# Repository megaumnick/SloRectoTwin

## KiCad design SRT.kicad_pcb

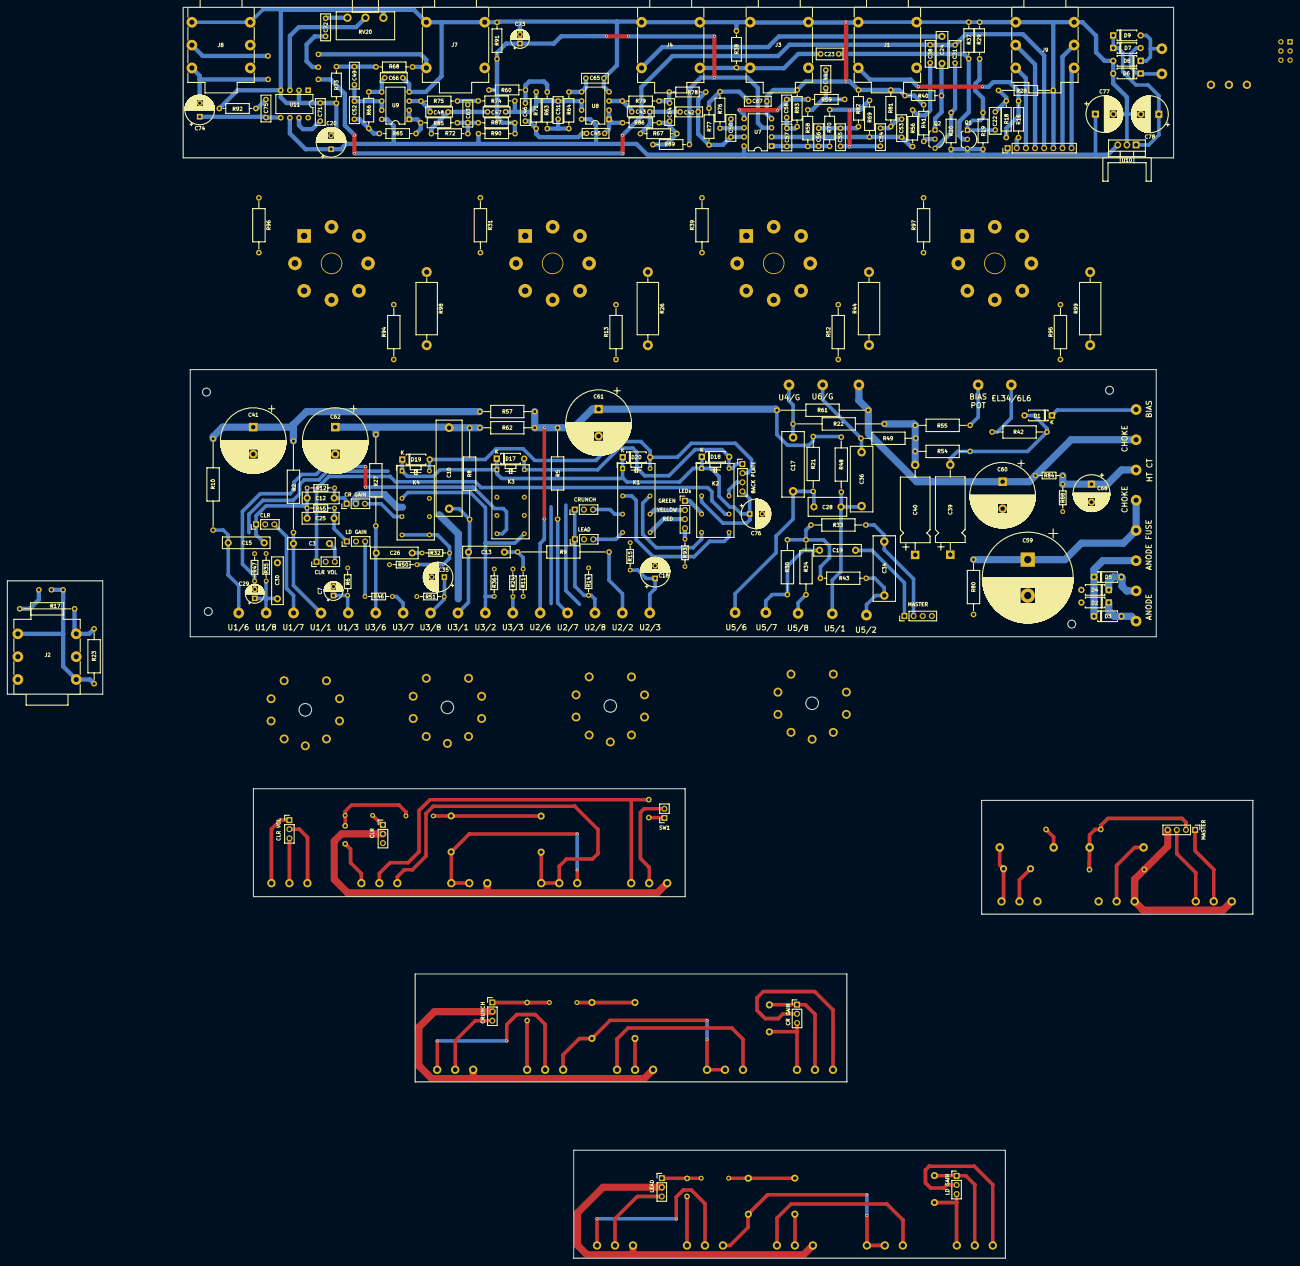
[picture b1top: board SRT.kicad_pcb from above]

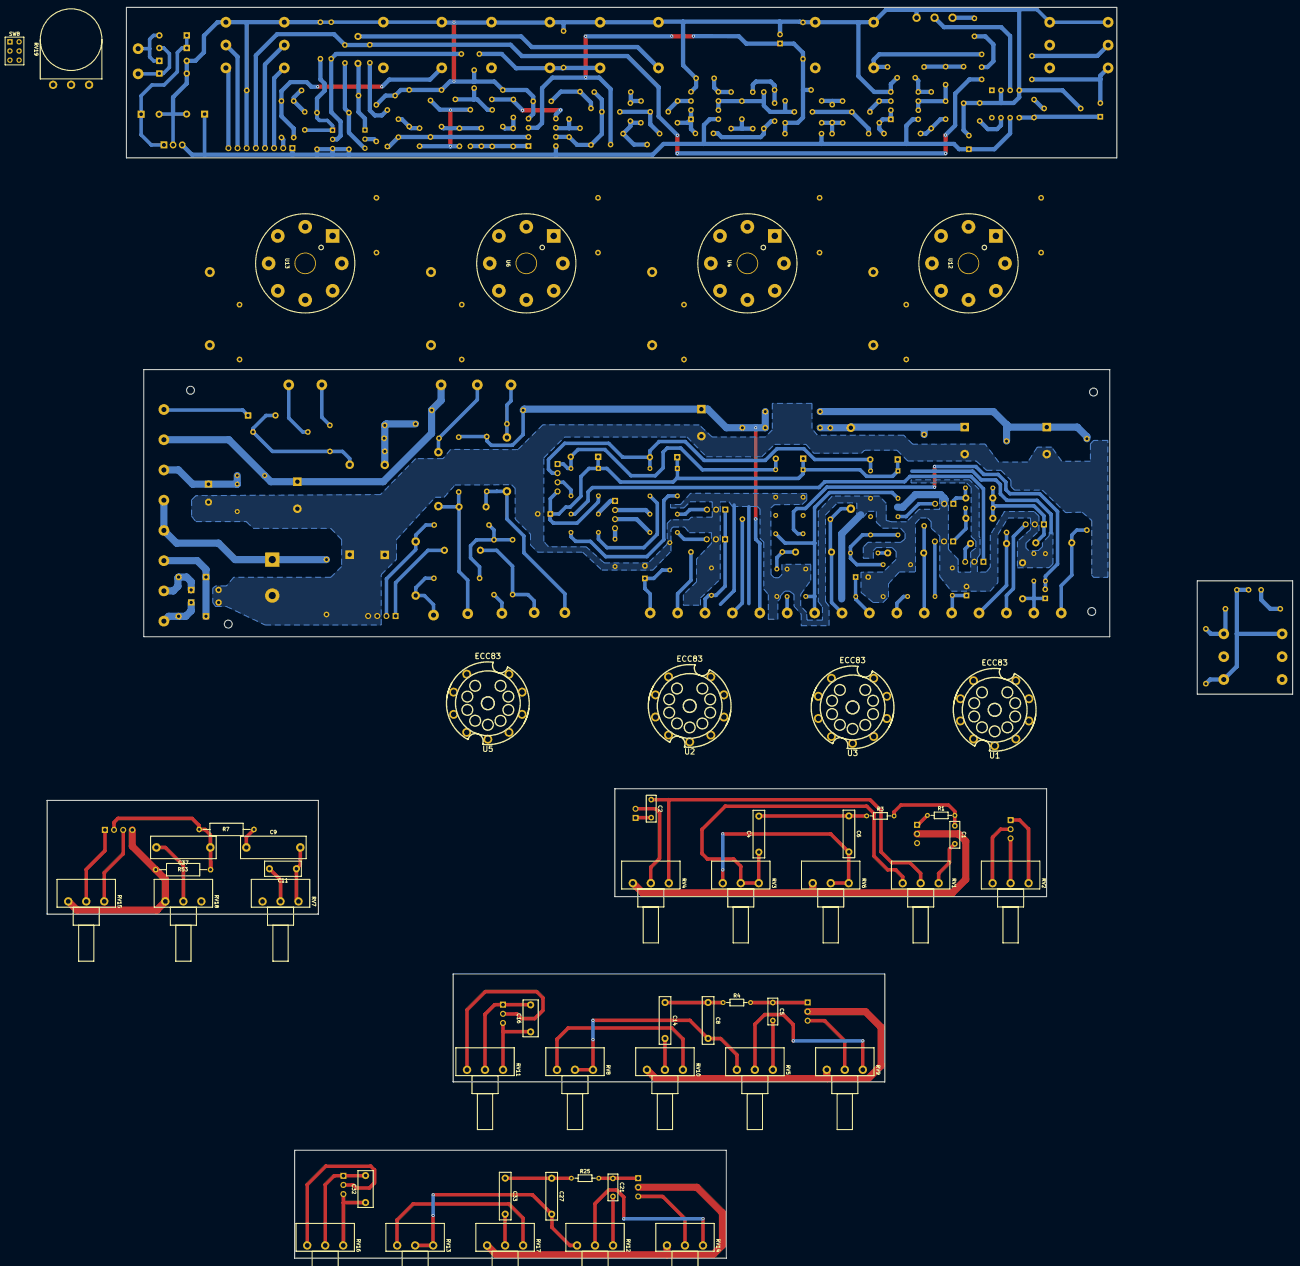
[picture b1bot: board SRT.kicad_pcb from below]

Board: 2 copper layers, 346.2 x 347.7 mm, 252 parts (49 on the bottom side), 158 nets.

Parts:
BACK PLATE: PinHeader_1x04_P2.54mm_Vertical
C1, C2: 220p; C_Rect_L7.2mm_W2.5mm_P5.00mm_FKS2_FKP2_MKS2_MKP2
C3, C6, C15: 47n; C_Rect_L13.0mm_W3.0mm_P10.00mm_FKS3_FKP3_MKS4
C4: 100n; C_Rect_L13.0mm_W3.0mm_P10.00mm_FKS3_FKP3_MKS4
C5: 470p; C_Rect_L7.2mm_W2.5mm_P5.00mm_FKS2_FKP2_MKS2_MKP2
C7, C29: 22uF; CP_Radial_D5.0mm_P2.50mm
C8, C13, C14, C19, C26, C27, C33: 22n; C_Rect_L13.0mm_W3.0mm_P10.00mm_FKS3_FKP3_MKS4
C9, C34, C37: 100n; C_Rect_L18.0mm_W6.0mm_P15.00mm_FKS3_FKP3
C10: 1000p; C_Rect_L26.5mm_W7.0mm_P22.50mm_MKS4
C11: 4n7; C_Rect_L10.0mm_W4.0mm_P7.50mm_FKS3_FKP3
C12: 470p; C_Rect_L10.0mm_W3.0mm_P7.50mm_FKS3_FKP3
C16, C32: 1000p; C_Rect_L10.0mm_W4.0mm_P7.50mm_FKS3_FKP3
C17, C36: 47n; C_Rect_L18.0mm_W6.0mm_P15.00mm_FKS3_FKP3
C18, C35: 1uF; CP_Radial_D8.0mm_P3.50mm
C20: 470uF; CP_Radial_D8.0mm_P3.80mm
C21: 680p; C_Rect_L7.2mm_W2.5mm_P5.00mm_FKS2_FKP2_MKS2_MKP2
C22: 100n; C_Rect_L7.2mm_W3.0mm_P5.00mm_FKS2_FKP2_MKS2_MKP2
C23: 1uF; C_Rect_L7.2mm_W3.0mm_P5.00mm_FKS2_FKP2_MKS2_MKP2
C24: 100n; C_Rect_L10.0mm_W3.0mm_P7.50mm_FKS3_FKP3
C25: 2200p; C_Rect_L10.0mm_W3.0mm_P7.50mm_FKS3_FKP3
C28: 47pF; C_Disc_D10.5mm_W5.0mm_P7.50mm
C30: 470n; C_Rect_L13.0mm_W3.0mm_P10.00mm_FKS3_FKP3_MKS4
C31: 220n; C_Rect_L7.2mm_W3.0mm_P5.00mm_FKS2_FKP2_MKS2_MKP2
C38, C50: 10n; C_Rect_L7.2mm_W2.5mm_P5.00mm_FKS2_FKP2_MKS2_MKP2
C39, C40: 10uF; CP_Axial_L18.0mm_D8.0mm_P25.00mm_Horizontal
C41, C60, C61, C62: 47uF; CP_Radial_D18.0mm_P7.50mm
C42, C43, C47, C48, C57, C58: 1n; C_Rect_L7.2mm_W2.5mm_P5.00mm_FKS2_FKP2_MKS2_MKP2
C44, C51, C52, C63, C64: 2n2; C_Rect_L7.2mm_W2.5mm_P5.00mm_FKS2_FKP2_MKS2_MKP2
C45, C46: 22n; C_Rect_L7.2mm_W2.5mm_P5.00mm_FKS2_FKP2_MKS2_MKP2
C49: 2.2uF; C_Rect_L7.2mm_W2.5mm_P5.00mm_FKS2_FKP2_MKS2_MKP2
C53, C54, C55, C56: 4n7; C_Rect_L7.2mm_W2.5mm_P5.00mm_FKS2_FKP2_MKS2_MKP2
C59: 200uF; CP_Radial_D25.0mm_P10.00mm_SnapIn
C65, C66: 330p; C_Rect_L7.2mm_W2.5mm_P5.00mm_FKS2_FKP2_MKS2_MKP2
C67, C71: 100n; C_Rect_L7.2mm_W2.5mm_P5.00mm_FKS2_FKP2_MKS2_MKP2
C68, C77: 100uF; CP_Radial_D10.0mm_P5.00mm
C72: 220n; C_Rect_L7.2mm_W2.5mm_P5.00mm_FKS2_FKP2_MKS2_MKP2
C73: 100uF; CP_Radial_D5.0mm_P2.50mm
C74: 220uF; CP_Radial_D8.0mm_P3.80mm
C75: 47n; C_Rect_L7.2mm_W2.5mm_P5.00mm_FKS2_FKP2_MKS2_MKP2
C76: 10uF; CP_Radial_D8.0mm_P3.50mm
C78: 2200uF; CP_Radial_D10.0mm_P5.00mm
CLR: PinHeader_1x03_P2.54mm_Vertical
CLR VOL: PinHeader_1x03_P2.54mm_Vertical
CLR VOL#2: PinHeader_1x03_P2.54mm_Vertical
CLR#2: PinHeader_1x03_P2.54mm_Vertical
CR GAIN: PinHeader_1x03_P2.54mm_Vertical
CR GAIN#2: PinHeader_1x03_P2.54mm_Vertical
CRUNCH: PinHeader_1x03_P2.54mm_Vertical
CRUNCH#2: PinHeader_1x03_P2.54mm_Vertical
D1, D2, D3, D4, D5, D6, D7, D8, D9, D17, D18, D19, D20: 1N4007; D_A-405_P7.62mm_Horizontal
J1: PreampOut; Jack_6.35mm_Neutrik_NMJ4HCD2_Horizontal
J2: In; Jack_6.35mm_Neutrik_NMJ6HCD2_Horizontal
J3: Send; Jack_6.35mm_Neutrik_NMJ4HCD2_Horizontal
J4: Return; Jack_6.35mm_Neutrik_NMJ4HCD2_Horizontal
J7: LineOut; Jack_6.35mm_Neutrik_NMJ4HCD2_Horizontal
J8: Cab/Phones; Jack_6.35mm_Neutrik_NMJ6HCD2_Horizontal
J9: Footswitch; Jack_6.35mm_Neutrik_NMJ6HCD2_Horizontal
K1, K4: CR/LD; Relay_DPDT_Omron_G5V-2
K2, K3: CL/DR; Relay_DPDT_Omron_G5V-2
LD GAIN: PinHeader_1x03_P2.54mm_Vertical
LD GAIN#2: PinHeader_1x03_P2.54mm_Vertical
LEAD: PinHeader_1x03_P2.54mm_Vertical
LEAD#2: PinHeader_1x03_P2.54mm_Vertical
LEDs: PinHeader_1x04_P2.54mm_Vertical
MASTER: PinHeader_1x04_P2.54mm_Vertical
MASTER#2: PinHeader_1x04_P2.54mm_Vertical
Q1, Q2: BF245A; TO-92L_Inline_Wide
R1, R88: 68k; R_Axial_DIN0204_L3.6mm_D1.6mm_P7.62mm_Horizontal
R2, R8, R27: 100k; R_Axial_DIN0309_L9.0mm_D3.2mm_P25.40mm_Horizontal
R3, R14, R47: 100k; R_Axial_DIN0204_L3.6mm_D1.6mm_P7.62mm_Horizontal
R4: 33k; R_Axial_DIN0204_L3.6mm_D1.6mm_P7.62mm_Horizontal
R5, R9, R10, R22: 220k; R_Axial_DIN0309_L9.0mm_D3.2mm_P25.40mm_Horizontal
R6: 1k5; R_Axial_DIN0204_L3.6mm_D1.6mm_P7.62mm_Horizontal
R7: 39k; R_Axial_DIN0309_L9.0mm_D3.2mm_P15.24mm_Horizontal
R11: 330k; R_Axial_DIN0204_L3.6mm_D1.6mm_P7.62mm_Horizontal
R12, R32, R46, R84: 470k; R_Axial_DIN0204_L3.6mm_D1.6mm_P7.62mm_Horizontal
R13, R52, R94, R95: 2k2; R_Axial_DIN0309_L9.0mm_D3.2mm_P15.24mm_Horizontal
R15, R35, R51: 1k8; R_Axial_DIN0204_L3.6mm_D1.6mm_P7.62mm_Horizontal
R16: 220k; R_Axial_DIN0207_L6.3mm_D2.5mm_P10.16mm_Horizontal
R17: 68k; R_Axial_DIN0309_L9.0mm_D3.2mm_P15.24mm_Horizontal
R18: 430k; R_Axial_DIN0207_L6.3mm_D2.5mm_P10.16mm_Horizontal
R19, R29, R40: 1M; R_Axial_DIN0207_L6.3mm_D2.5mm_P10.16mm_Horizontal
R20, R37, R83: 10k; R_Axial_DIN0207_L6.3mm_D2.5mm_P10.16mm_Horizontal
R21, R80: 82k; R_Axial_DIN0309_L9.0mm_D3.2mm_P15.24mm_Horizontal
R23, R30: 1M; R_Axial_DIN0309_L9.0mm_D3.2mm_P15.24mm_Horizontal
R24: 39k; R_Axial_DIN0204_L3.6mm_D1.6mm_P7.62mm_Horizontal
R25: 47k; R_Axial_DIN0204_L3.6mm_D1.6mm_P7.62mm_Horizontal
R26, R44, R98, R99: 470; R_Axial_DIN0614_L14.3mm_D5.7mm_P20.32mm_Horizontal
R28: 39k; R_Axial_DIN0207_L6.3mm_D2.5mm_P15.24mm_Horizontal
R31, R39, R96, R97: 1R; R_Axial_DIN0309_L9.0mm_D3.2mm_P15.24mm_Horizontal
R33: 10k; R_Axial_DIN0309_L9.0mm_D3.2mm_P15.24mm_Horizontal
R34: 470; R_Axial_DIN0309_L9.0mm_D3.2mm_P15.24mm_Horizontal
R36, R50: 2M2; R_Axial_DIN0204_L3.6mm_D1.6mm_P7.62mm_Horizontal
R38, R73: 100k; R_Axial_DIN0207_L6.3mm_D2.5mm_P10.16mm_Horizontal
R41: 2k4; R_Axial_DIN0207_L6.3mm_D2.5mm_P10.16mm_Horizontal
R42, R54, R57, R62: 15k; R_Axial_DIN0309_L9.0mm_D3.2mm_P15.24mm_Horizontal
R43: 1M; R_Axial_DIN0309_L9.0mm_D3.2mm_P12.70mm_Horizontal
R45: 680k; R_Axial_DIN0204_L3.6mm_D1.6mm_P7.62mm_Horizontal
R48: 100k; R_Axial_DIN0309_L9.0mm_D3.2mm_P15.24mm_Horizontal
R49: 220k; R_Axial_DIN0309_L9.0mm_D3.2mm_P15.24mm_Horizontal
R53: 4k7; R_Axial_DIN0309_L9.0mm_D3.2mm_P15.24mm_Horizontal
R55: 56k; R_Axial_DIN0309_L9.0mm_D3.2mm_P15.24mm_Horizontal
R56: 240k; R_Axial_DIN0207_L6.3mm_D2.5mm_P10.16mm_Horizontal
R58: 18k7; R_Axial_DIN0207_L6.3mm_D2.5mm_P10.16mm_Horizontal
R59, R65, R66, R69: 20k; R_Axial_DIN0207_L6.3mm_D2.5mm_P10.16mm_Horizontal
R60: 200k; R_Axial_DIN0207_L6.3mm_D2.5mm_P10.16mm_Horizontal
R61: 10k; R_Axial_DIN0309_L9.0mm_D3.2mm_P25.40mm_Horizontal
R63, R64: 22k; R_Axial_DIN0207_L6.3mm_D2.5mm_P10.16mm_Horizontal
R67: 12.7k; R_Axial_DIN0207_L6.3mm_D2.5mm_P10.16mm_Horizontal
R68: 1k; R_Axial_DIN0207_L6.3mm_D2.5mm_P10.16mm_Horizontal
R70, R76, R77: 36k; R_Axial_DIN0207_L6.3mm_D2.5mm_P10.16mm_Horizontal
R71: 82k; R_Axial_DIN0207_L6.3mm_D2.5mm_P10.16mm_Horizontal
R72: 6.2k; R_Axial_DIN0207_L6.3mm_D2.5mm_P10.16mm_Horizontal
R74: 11k; R_Axial_DIN0207_L6.3mm_D2.5mm_P10.16mm_Horizontal
R75: 15k; R_Axial_DIN0207_L6.3mm_D2.5mm_P10.16mm_Horizontal
R78, R79: 24k; R_Axial_DIN0207_L6.3mm_D2.5mm_P10.16mm_Horizontal
R81: 6k8; R_Axial_DIN0207_L6.3mm_D2.5mm_P10.16mm_Horizontal
R82: 820; R_Axial_DIN0207_L6.3mm_D2.5mm_P10.16mm_Horizontal
R85: 150; R_Axial_DIN0207_L6.3mm_D2.5mm_P10.16mm_Horizontal
R86: 100; R_Axial_DIN0207_L6.3mm_D2.5mm_P10.16mm_Horizontal
R87: 1k8; R_Axial_DIN0207_L6.3mm_D2.5mm_P10.16mm_Horizontal
R89: 4k12; R_Axial_DIN0207_L6.3mm_D2.5mm_P10.16mm_Horizontal
R90: 470k; R_Axial_DIN0207_L6.3mm_D2.5mm_P10.16mm_Horizontal
R91: 68k; R_Axial_DIN0207_L6.3mm_D2.5mm_P10.16mm_Horizontal
R92: 10; R_Axial_DIN0207_L6.3mm_D2.5mm_P10.16mm_Horizontal
R93: 2k2; R_Axial_DIN0204_L3.6mm_D1.6mm_P7.62mm_Horizontal
RV1, RV5, RV12: B250k; Potentiometer_Piher_T-16H_Single_Horizontal
RV2, RV4, RV7, RV8, RV9, RV11, RV13, RV14, RV16, RV20: A1M; Potentiometer_Piher_T-16H_Single_Horizontal
RV3, RV15: A250k; Potentiometer_Piher_T-16H_Single_Horizontal
RV6: B10k; Potentiometer_Piher_T-16H_Single_Horizontal
RV10, RV18: B25k; Potentiometer_Piher_T-16H_Single_Horizontal
RV17: B50k; Potentiometer_Piher_T-16H_Single_Horizontal
RV19: B25k; Potentiometer_Omeg_PC16BU_Vertical
SW1: Bright; PinSocket_1x02_P2.54mm_Vertical
SW8: SW_Push_DPDT; SW_NKK_G1xJP
U1, U2, U3, U5: ECC83; socket_gzc9-b
U4, U6, U12, U13: EL34; Valve_Octal
U7, U8, U9: TL062; DIP-8_W7.62mm
U10: L7812; TO-220-3_Vertical
U11: LM386; DIP-8_W7.62mm

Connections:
1/2: C73.1, R60.1, R87.2, R89.2, R90.1, R91.2, U7.3 (+)
+12V: BACK PLATE.4, C20.1, C76.1, C77.1, D17.1 (K), D18.1 (K), D19.1 (K), D20.1 (K), K1.1, K2.1, K2.4, K3.1, K4.1, Q1.3 (D), R19.2, R20.2, R90.2, U7.8 (V+), U8.8 (V+), U9.8 (V+), U10.3 (OUT), U11.6 (V+)
B+1: C41.1, R2.2, R10.2, R57.2
B+2: C10.1, C62.1, R8.2, R27.2, R62.2
B+3: C61.1, R5.2, R21.1, R48.2, R57.1, R61.2, R62.1, U2.6 (A)
B+4: C60.1, R26.2, R44.1, R61.1, R84.2, R98.2, R99.1
B+5: C59.1, R80.1
BIAS: C40.2, R22.1, R49.2, R54.1, R55.2
GND: C7.2, C18.2, C20.2, C30.2, C35.2, C39.1, C40.1, C41.2, C44.2, C59.2, C60.2, C61.2, C62.2, C65.2, C66.2, C67.2, C68.2, C71.2, C73.2, C76.2, C77.2, C78.2, CLR.2, CLR VOL.2, CLR VOL#2.2, CLR#2.2, CR GAIN.2, CR GAIN#2.2, CRUNCH.2, CRUNCH#2.2, D2.2 (A), D4.2 (A), D6.2 (A), D8.2 (A), J1.S, J1.SN, J2.S, J2.TN, J3.S, J3.SN, J4.S, J4.SN, J7.S, J7.SN, J8.S, J8.SN, J9.S, J9.SN, K3.4, K3.13, K4.13, LD GAIN.2, LD GAIN#2.2, LEAD.2, LEAD#2.2, MASTER.4, MASTER#2.3, MASTER#2.4, R6.1, R11.1, R14.1, R15.1, R23.1, R24.1, R28.1, R29.1, R31.1, R35.1, R36.1, R37.1, R38.1, R39.2, R40.1, R41.1, R47.1, R50.1, R51.1, R53.1, R73.2, R80.2, R81.2, R82.2, R83.2, R88.1, R91.1, R92.2, R93.1, R96.1, R97.2, RV2.1, RV4.1, RV6.1, RV9.1, RV10.1, RV11.1, RV14.1, RV15.1, RV16.1, RV17.1, RV18.1, RV19.1, RV19.2, RV20.1, SW8.2 (B), SW8.5 (B), U7.4 (V-), U8.4 (V-), U9.4 (V-), U10.2 (GND), U11.2 (-), U11.4 (GND)
unnamed: C1.1, R1.2, R3.2
unnamed: C1.2, RV1.3
unnamed: C2.1, RV1.2, RV4.3
unnamed: C2.2, SW1.1
unnamed: C3.2, CLR VOL.1, CLR VOL#2.3, RV2.3
unnamed: C4.1, RV1.1, RV3.2, RV3.3
unnamed: C4.2, C6.1, R3.1
unnamed: C5.2, RV5.3
unnamed: C6.2, RV3.1, RV6.2, RV6.3
unnamed: C8.2, RV5.1, RV8.2, RV8.3
unnamed: C9.1, R7.2
unnamed: C9.2, C11.1, RV7.3
unnamed: C11.2, RV7.2
unnamed: C12.1, C16.1, CR GAIN.1, CR GAIN#2.3, R12.1, RV11.3
unnamed: C12.2, C15.2, C25.1, CLR.1, CLR#2.1, R1.1, R12.2, R45.1
unnamed: C13.2, R9.2, R11.2
unnamed: C8.1, C14.1, R4.1
unnamed: C14.2, RV10.2
unnamed: C16.2, CR GAIN.3, CR GAIN#2.1, K4.6, RV11.2
unnamed: C17.1, R13.1, R22.2, R94.1
unnamed: C19.1, MASTER.1, MASTER#2.1, RV15.2
unnamed: C21.2, RV12.3
unnamed: C22.1, R18.1, R28.2
unnamed: C23.2, J3.T, J4.TN, R38.2
unnamed: C24.1, J4.T
unnamed: C25.2, C32.1, LD GAIN.3, LD GAIN#2.1, R45.2, RV16.3
unnamed: C26.2, R32.1
unnamed: C27.1, C33.1, R25.1
unnamed: C27.2, RV12.1, RV13.2, RV13.3
unnamed: C29.2, K3.8, R47.2
unnamed: C32.2, LD GAIN.1, LD GAIN#2.3, R46.1, RV16.2
unnamed: C33.2, RV17.2
unnamed: C34.1, C37.1, MASTER.2, MASTER#2.2, R7.1, R33.1, R53.2
unnamed: C36.2, R49.1, R52.1, R95.1
unnamed: C37.2, RV18.2
unnamed: C38.1, R56.1
unnamed: C42.1, C50.2, R77.1, R78.2, U7.7
unnamed: C42.2, C43.1, R67.1
unnamed: C44.1, R58.1, R59.2
unnamed: C45.2, C46.1, R71.1
unnamed: C46.2, R60.2, R63.2
unnamed: C47.2, C48.1, R72.1
unnamed: C49.2, R68.2, R73.1
unnamed: C51.1, R63.1, R64.2
unnamed: C52.1, R65.1, R66.2
unnamed: C53.2, C54.1, R81.1
unnamed: C54.2, C55.1, R69.1, R70.2
unnamed: C55.2, C56.1, R82.1
unnamed: C56.2, C57.1, R58.2, R70.1, U7.1
unnamed: C57.2, C58.1, R83.1
unnamed: C63.1, R74.1, R75.2
unnamed: C63.2, R72.2, R85.2, R87.1
unnamed: C64.1, R78.1, R79.2
unnamed: C64.2, R67.2, R86.2, R89.1
unnamed: C67.1, R76.1, R77.2
unnamed: C68.1, R84.1, R88.2
unnamed: C72.2, RV20.3
unnamed: C74.1, C75.2, U11.5
unnamed: C75.1, R92.1
unnamed: C39.2, D1.2 (A), R42.2, R54.2
unnamed: D2.1 (K), D3.2 (A)
unnamed: D3.1 (K), D5.1 (K)
unnamed: D4.1 (K), D5.2 (A)
unnamed: D6.1 (K), D7.2 (A)
unnamed: C78.1, D7.1 (K), D9.1 (K), U10.1 (IN)
unnamed: D8.1 (K), D9.2 (A)
unnamed: BACK PLATE.1, D17.2 (A), D18.2 (A), J9.R, K2.16, K3.16
unnamed: BACK PLATE.2, D19.2 (A), D20.2 (A), J9.T, K1.16, K4.16
unnamed: J1.T, R16.1, R18.2
unnamed: J2.T, R17.1, R23.2
unnamed: K1.4, K2.9
unnamed: CRUNCH.3, CRUNCH#2.3, K1.6, RV9.2
unnamed: K1.8, LEAD.3, LEAD#2.3, RV14.2
unnamed: K1.9, LEDs.3
unnamed: K1.11, LEDs.2
unnamed: K1.13, K2.8
unnamed: K2.6, LEDs.1
unnamed: CLR VOL.3, CLR VOL#2.1, K2.11, RV2.2
unnamed: BACK PLATE.3, K2.13, R16.2
unnamed: K4.8, K4.9, R32.2, R50.2
unnamed: C22.2, Q1.1 (G), R19.1, R29.2
unnamed: C23.1, Q1.2 (S), R37.2
unnamed: C31.1, Q2.3 (D), R20.1
unnamed: C24.2, Q2.1 (G), R40.2
unnamed: Q2.2 (S), R41.2
unnamed: R30.1, R33.2, R34.1, R43.2
unnamed: R42.1, SW8.1 (A), SW8.4 (A)
unnamed: R55.1, RV19.3
unnamed: LEDs.4, R93.2
unnamed: RV5.2, RV9.3
unnamed: RV8.1, RV10.3
unnamed: RV12.2, RV14.3
unnamed: RV13.1, RV17.3
unnamed: J7.T, R68.1
unnamed: C31.2, C38.2, MASTER.3, RV15.3
unnamed: C74.2, J8.T
unnamed: SW8.3 (C), SW8.6 (C)
unnamed: C15.1, R10.1, U1.6 (A)
unnamed: CLR.3, CLR#2.3, R17.2, U1.7 (G)
unnamed: C29.1, C30.1, R35.2, U1.8 (K)
unnamed: C3.1, R2.1, U1.1 (A)
unnamed: RV4.2, SW1.2, U1.2 (G)
unnamed: C7.1, R6.2, U1.3 (K)
unnamed: U1.4 (F1), U2.4 (F1), U3.4 (F1), U5.4 (F1)
unnamed: U1.5 (F1), U2.5 (F1), U3.5 (F1), U5.5 (F1)
unnamed: R5.1, U2.1 (A), U2.7 (G)
unnamed: C5.1, C21.1, CRUNCH.1, CRUNCH#2.1, LEAD.1, LEAD#2.1, R4.2, R14.2, R25.2, U2.8 (K)
unnamed: R9.1, U2.2 (G)
unnamed: C18.1, R15.2, U2.3 (K)
unnamed: C26.1, R27.1, U3.6 (A)
unnamed: R46.2, U3.7 (G)
unnamed: C35.1, R51.2, U3.8 (K)
unnamed: C10.2, C13.1, R8.1, U3.1 (A)
unnamed: K3.9, K4.4, R36.2, U3.2 (G)
unnamed: R24.2, U3.3 (K)
unnamed: R31.2, U4.8 (F1)
unnamed: R13.2, U4.5 (G1)
unnamed: R26.1, U4.4 (G2)
unnamed: C17.2, C28.2, R21.2, U5.6 (A)
unnamed: C19.2, R30.2, U5.7 (G)
unnamed: R34.2, U5.3 (K), U5.8 (K)
unnamed: C28.1, C36.1, R48.1, U5.1 (A)
unnamed: C34.2, R43.1, U5.2 (G)
unnamed: R39.1, U6.8 (F1)
unnamed: R52.2, U6.5 (G1)
unnamed: R44.2, U6.4 (G2)
unnamed: C53.1, R56.2, R69.2, U7.2 (-)
unnamed: C58.2, R59.1, U7.5 (+)
unnamed: C50.1, R76.2, U7.6 (-)
unnamed: C43.2, R79.1, U8.3 (+)
unnamed: C45.1, R86.1, U8.1, U8.2 (-)
unnamed: C65.1, R64.1, U8.5 (+)
unnamed: C47.1, C51.2, R71.2, R74.2, U8.6 (-), U8.7
unnamed: C48.2, R75.1, U9.3 (+)
unnamed: R65.2, R85.1, U9.1, U9.2 (-)
unnamed: C66.1, R66.1, U9.5 (+)
unnamed: C49.1, C52.2, U9.6 (-), U9.7
unnamed: RV20.2, U11.3 (+)
unnamed: C71.1, U11.7 (BYPASS)
unnamed: U4.3 (A), U12.3 (A)
unnamed: R96.2, U12.8 (F1)
unnamed: R94.2, U12.5 (G1)
unnamed: R98.1, U12.4 (G2)
unnamed: U4.2 (F1), U6.2 (F1), U12.2 (F1), U13.2 (F1)
unnamed: U4.7 (F2), U6.7 (F2), U12.7 (F2), U13.7 (F2)
unnamed: U6.3 (A), U13.3 (A)
unnamed: R97.1, U13.8 (F1)
unnamed: R95.2, U13.5 (G1)
unnamed: R99.2, U13.4 (G2)

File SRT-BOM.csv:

"#","Reference","Value","Напряжение","Material"
"1","C78","2200uF","25V","Elec"
"2","C77","100uF","16V","Elec"
"3","C76","10uF","16V","Elec"
"4","C74","220uF","100V","Elec"
"5","C73","100uF","16V","Elec"
"6","C68","100uF","100V","Elec"
"7","C62","47uF","450V","Elec"
"8","C61","47uF","450V","Elec"
"9","C60","47uF","450V","Elec"
"10","C59","200uF","450V","Elec"
"11","C49","2.2uF","100V","Elec"
"12","C41","47uF","450V","Elec"
"13","C40","10uF","100V","Elec"
"14","C39","10uF","100V","Elec"
"15","C35","1uF","100V","Elec"
"16","C29","22uF","100V","Elec"
"17","C20","470uF","16V","Elec"
"18","C18","1uF","100V","Elec"
"19","C7","22uF","100V","Elec"
"20","U13","EL34","",""
"21","U12","EL34","",""
"22","U11","LM386","",""
"23","U10","L7812","",""
"24","U9","TL062","",""
"25","U8","TL062","",""
"26","U7","TL062","",""
"27","U6","EL34","",""
"28","U5","ECC83","",""
"29","U4","EL34","",""
"30","U3","ECC83","",""
"31","U2","ECC83","",""
"32","U1","ECC83","",""
"33","T3","Power","",""
"34","T2","10H","",""
"35","T1","Sound","",""
"36","SW8","SW_Push_DPDT","",""
"37","SW7","CL/DR","",""
"38","SW6","CR/LD","",""
"39","SW5","Cab/Phones","",""
"40","SW4","Power","",""
"41","SW3","STDB","",""
"42","SW2","Selector","",""
"43","SW1","Bright","",""
"44","RV20","A1M","",""
"45","RV19","B25k","",""
"46","RV18","B25k","",""
"47","RV17","B50k","",""
"48","RV16","A1M","",""
"49","RV15","A250k","",""
"50","RV14","A1M","",""
"51","RV13","A1M","",""
"52","RV12","B250k","",""
"53","RV11","A1M","",""
"54","RV10","B25k","",""
"55","RV9","A1M","",""
"56","RV8","A1M","",""
"57","RV7","A1M","",""
"58","RV6","B10k","",""
"59","RV5","B250k","",""
"60","RV4","A1M","",""
"61","RV3","A250k","",""
"62","RV2","A1M","",""
"63","RV1","B250k","",""
"64","R99","470","",""
"65","R98","470","",""
"66","R97","1R","",""
"67","R96","1R","",""
"68","R95","2k2","",""
"69","R94","2k2","",""
"70","R93","2k2","",""
"71","R92","10","",""
"72","R91","68k","",""
"73","R90","470k","",""
"74","R89","4k12","",""
"75","R88","68k","",""
"76","R87","1k8","",""
"77","R86","100","",""
"78","R85","150","",""
"79","R84","470k","",""
"80","R83","10k","",""
"81","R82","820","",""
"82","R81","6k8","",""
"83","R80","82k","",""
"84","R79","24k","",""
"85","R78","24k","",""
"86","R77","36k","",""
"87","R76","36k","",""
"88","R75","15k","",""
"89","R74","11k","",""
"90","R73","100k","",""
"91","R72","6.2k","",""
"92","R71","82k","",""
"93","R70","36k","",""
"94","R69","20k","",""
"95","R68","1k","",""
"96","R67","12.7k","",""
"97","R66","20k","",""
"98","R65","20k","",""
"99","R64","22k","",""
"100","R63","22k","",""
"101","R62","15k","",""
"102","R61","10k","",""
"103","R60","200k","",""
"104","R59","20k","",""
"105","R58","18k7","",""
"106","R57","15k","",""
"107","R56","240k","",""
"108","R55","56k","",""
"109","R54","15k","",""
"110","R53","4k7","",""
"111","R52","2k2","",""
"112","R51","1k8","",""
"113","R50","2M2","",""
"114","R49","220k","",""
"115","R48","100k","",""
"116","R47","100k","",""
"117","R46","470k","",""
"118","R45","680k","",""
"119","R44","470","",""
"120","R43","1M","",""
"121","R42","15k","",""
"122","R41","2k4","",""
"123","R40","1M","",""
"124","R39","1R","",""
"125","R38","100k","",""
"126","R37","10k","",""
"127","R36","2M2","",""
"128","R35","1k8","",""
"129","R34","470","",""
"130","R33","10k","",""
"131","R32","470k","",""
"132","R31","1R","",""
"133","R30","1M","",""
"134","R29","1M","",""
"135","R28","39k","",""
"136","R27","100k","",""
"137","R26","470","",""
"138","R25","47k","",""
"139","R24","39k","",""
"140","R23","1M","",""
"141","R22","220k","",""
"142","R21","82k","",""
"143","R20","10k","",""
"144","R19","1M","",""
"145","R18","430k","",""
"146","R17","68k","",""
"147","R16","220k","",""
"148","R15","1k8","",""
"149","R14","100k","",""
"150","R13","2k2","",""
"151","R12","470k","",""
"152","R11","330k","",""
"153","R10","220k","",""
"154","R9","220k","",""
"155","R8","100k","",""
"156","R7","39k","",""
"157","R6","1k5","",""
"158","R5","220k","",""
"159","R4","33k","",""
"160","R3","100k","",""
"161","R2","100k","",""
"162","R1","68k","",""
"163","Q2","BF245A","",""
"164","Q1","BF245A","",""
"165","P1","Conn_WallPlug_Earth","",""
"166","NE1","Lamp_Neon","",""
"167","K4","CR/LD","",""
"168","K3","CL/DR","",""
"169","K2","CL/DR","",""
"170","K1","CR/LD","",""
"171","J9","Footswitch","",""
"172","J8","Cab/Phones","",""
"173","J7","LineOut","",""
"174","J6","Out","",""
"175","J5","Out","",""
"176","J4","Return","",""
"177","J3","Send","",""
"178","J2","In","",""
"179","J1","PreampOut","",""
"180","F2","Fuse","",""
"181","F1","Fuse","",""
"182","D20","1N4007","",""
"183","D19","1N4007","",""
"184","D18","1N4007","",""
"185","D17","1N4007","",""
"186","D12","GREEN","",""
"187","D11","YELLOW","",""
"188","D10","RED","",""
"189","D9","1N4007","",""
"190","D8","1N4007","",""
"191","D7","1N4007","",""
"192","D6","1N4007","",""
"193","D5","1N4007","",""
"194","D4","1N4007","",""
"195","D3","1N4007","",""
"196","D2","1N4007","",""
"197","D1","1N4007","",""
"198","C75","47n","100V",""
"199","C72","220n","100V",""
"200","C71","100n","100V",""
"201","C67","100n","100V",""
"202","C66","330p","100V",""
"203","C65","330p","100V",""
"204","C64","2n2","100V",""
"205","C63","2n2","100V",""
"206","C58","1n","100V",""
"207","C57","1n","100V",""
"208","C56","4n7","100V",""
"209","C55","4n7","100V",""
"210","C54","4n7","100V",""
"211","C53","4n7","100V",""
"212","C52","2n2","100V",""
"213","C51","2n2","100V",""
"214","C50","10n","100V",""
"215","C48","1n","100V",""
"216","C47","1n","100V",""
"217","C46","22n","100V",""
"218","C45","22n","100V",""
"219","C44","2n2","100V",""
"220","C43","1n","100V",""
"221","C42","1n","100V",""
"222","C38","10n","100V",""
"223","C37","100n","450V",""
"224","C36","47n","450V",""
"225","C34","100n","450V",""
"226","C33","22n","450V",""
"227","C32","1000p","450V",""
"228","C31","220n","100V",""
"229","C30","470n","100V",""
"230","C28","47pF","450V",""
"231","C27","22n","450V",""
"232","C26","22n","450V",""
"233","C25","2200p","450V",""
"234","C24","100n","100V",""
"235","C23","1uF","100V",""
"236","C22","100n","100V",""
"237","C21","680p","450V",""
"238","C19","22n","450V",""
"239","C17","47n","450V",""
"240","C16","1000p","450V",""
"241","C15","47n","450V",""
"242","C14","22n","450V",""
"243","C13","22n","450V",""
"244","C12","470p","450V",""
"245","C11","4n7","450V",""
"246","C10","1000p","450V",""
"247","C9","100n","450V",""
"248","C8","22n","450V",""
"249","C6","47n","450V",""
"250","C5","470p","450V",""
"251","C4","100n","450V",""
"252","C3","47n","450V",""
"253","C2","220p","450V",""
"254","C1","220p","450V",""

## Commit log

2026-04-25 Initial request
2026-05-03 Изменён формат 3D моделей после обновления версии Kicad
